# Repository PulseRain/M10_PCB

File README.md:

# M10_PCB
PCB Design File for PulseRain M10 board

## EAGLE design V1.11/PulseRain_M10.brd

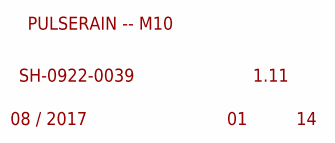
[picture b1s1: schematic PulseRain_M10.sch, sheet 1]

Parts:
GND: PULSERAIN_LOGO_BIGGER

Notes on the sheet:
1.11
SH-0922-0039
PULSERAIN -- M10
08 / 2017

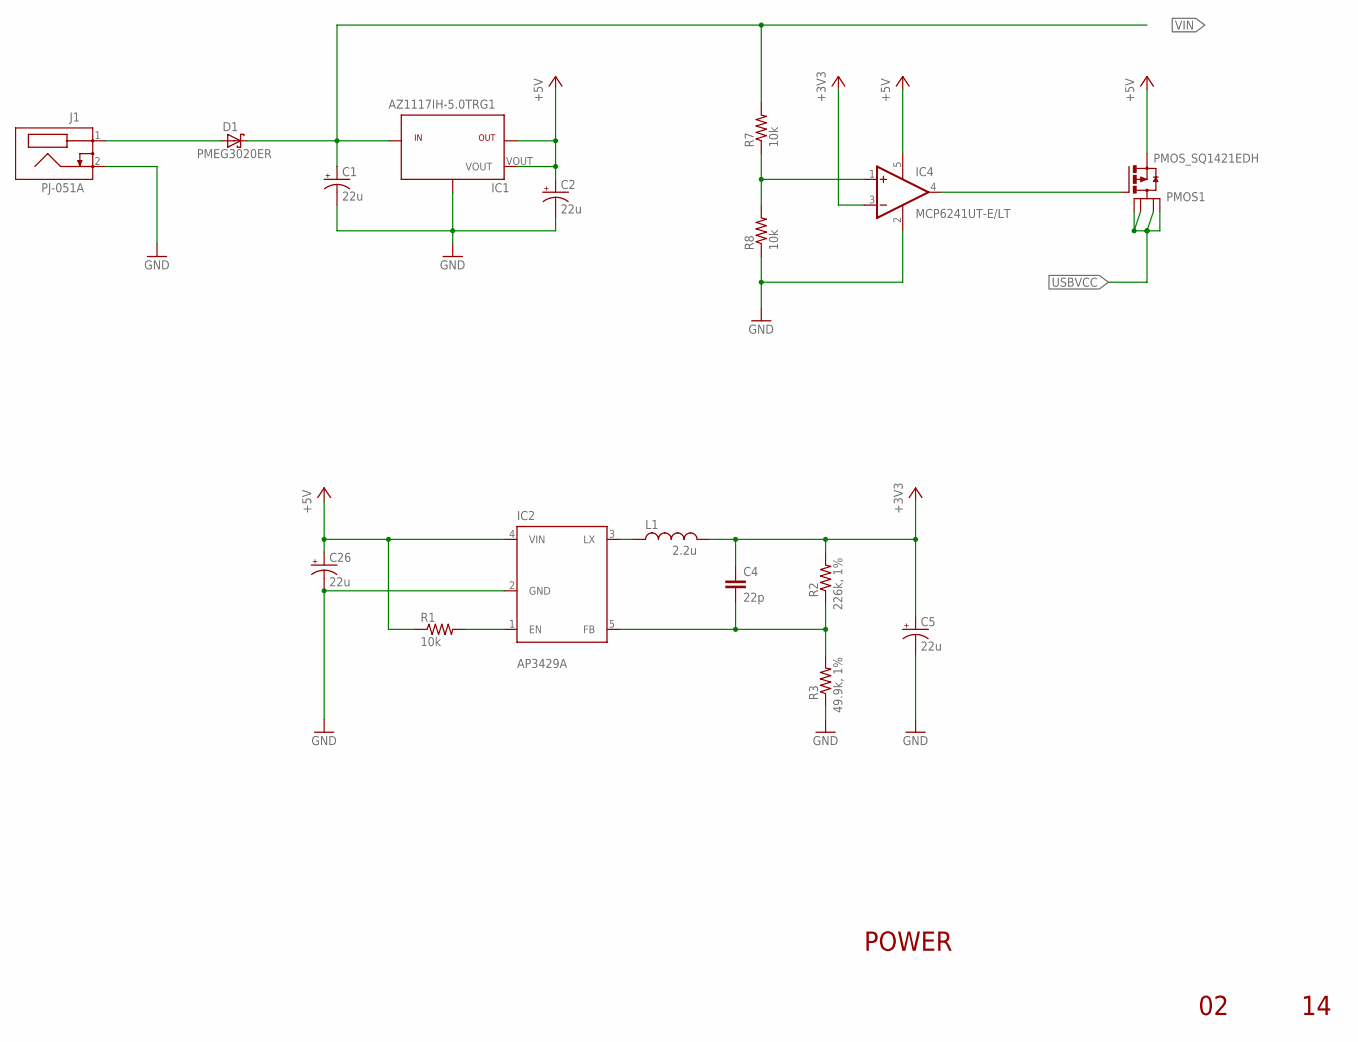
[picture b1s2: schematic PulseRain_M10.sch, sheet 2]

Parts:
C1, C2, C5, C26: 22u; PANASONIC_B
C4: 22p; 0603-CAP
D1: PMEG3020ER; SOD123W
IC1: AZ1117IH-5.0TRG1; SOT223
IC2: AP3429A; TSOT25
IC4: MCP6241UT-E/LT; SC-70-5
J1: PJ-051A
L1: 2.2u; DFE252012C
PMOS1: PMOS_SQ1421EDH; SC70-6L
R1, R7, R8: 10k; VISHAY-R-0603
R2: 226k, 1%; VISHAY-R-0603
R3: 49.9k, 1%; VISHAY-R-0603

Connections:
+3V3: C4.1, C5.+, IC4.3 (-IN), L1.2, R2.P$2 (2); also elsewhere on the board
+5V: C2.+, C26.+, IC1.2, IC1.VOUT, IC2.4 (VIN), IC4.5 (V+), PMOS1.4 (S), R1.P$1 (1); also elsewhere on the board
GND: C1.-, C2.-, C5.-, C26.-, IC1.1, IC2.2 (GND), IC4.2 (V-), J1.2, R3.P$1 (1), R8.P$1 (1); also elsewhere on the board
unnamed: D1.2, J1.1
unnamed: IC4.1 (+IN), R7.P$1 (1), R8.P$2 (2)
unnamed: IC2.3 (LX), L1.1
unnamed: IC2.1 (EN), R1.P$2 (2)
unnamed: C4.2, IC2.5 (FB), R2.P$1 (1), R3.P$2 (2)
unnamed: IC4.4 (OUT), PMOS1.3 (G)
USBVCC: PMOS1.1 (D1), PMOS1.2 (D2), PMOS1.5 (D3), PMOS1.6 (D4); also elsewhere on the board
VIN: C1.+, D1.1, IC1.3, R7.P$2 (2); also elsewhere on the board

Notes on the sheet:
POWER

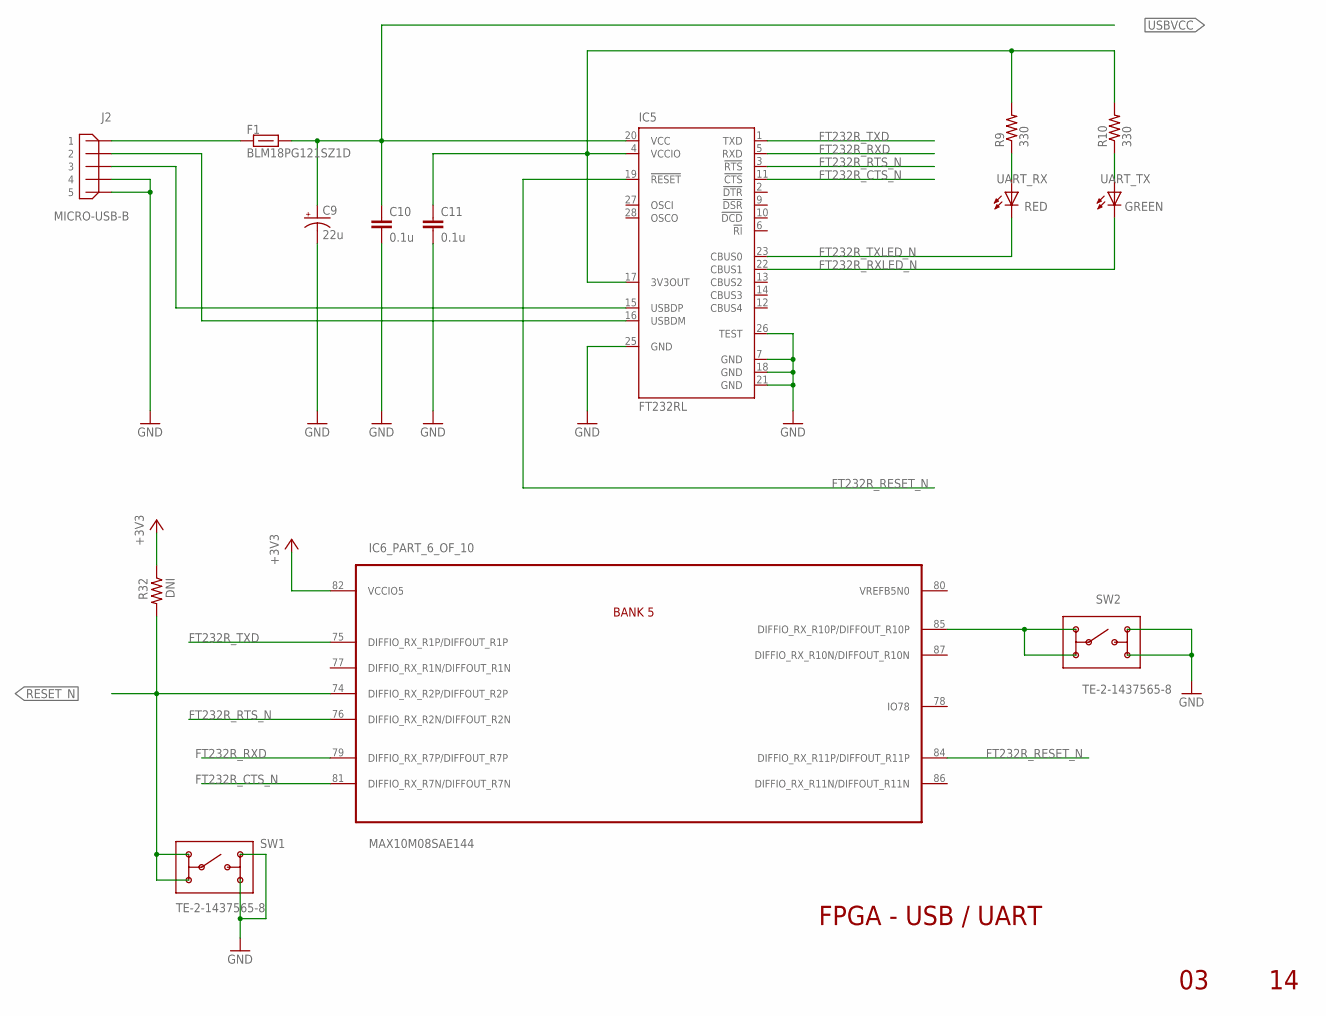
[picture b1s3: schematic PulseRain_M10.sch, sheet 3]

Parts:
C9: 22u; PANASONIC_B
C10, C11: 0.1u; 0603-CAP
F1: BLM18PG121SZ1D; 0603-BEAD
IC5: FT232RL; SSOP28
IC6: MAX10M08SAE144; EQFP144
J2: MICRO-USB-B; SD-47346-001
R9, R10: 330; VISHAY-R-0603
R32: DNI; VISHAY-R-0603
SW1, SW2: TE-2-1437565-8
UART_RX: RED; HARVATEK_0603
UART_TX: GREEN; HARVATEK_0603

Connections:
+3V3: IC6.82 (VCCIO5), R32.P$1 (1); also elsewhere on the board
FT232R_CTS_N: IC5.11 (!CTS), IC6.81 (DIFFIO_RX_R7N/DIFFOUT_R7N)
FT232R_RESET_N: IC5.19 (!RESET), IC6.84 (DIFFIO_RX_R11P/DIFFOUT_R11P)
FT232R_RTS_N: IC5.3 (!RTS), IC6.76 (DIFFIO_RX_R2N/DIFFOUT_R2N)
FT232R_RXD: IC5.5 (RXD), IC6.79 (DIFFIO_RX_R7P/DIFFOUT_R7P)
FT232R_RXLED_N: IC5.22 (CBUS1), UART_TX.C
FT232R_TXD: IC5.1 (TXD), IC6.75 (DIFFIO_RX_R1P/DIFFOUT_R1P)
FT232R_TXLED_N: IC5.23 (CBUS0), UART_RX.C
GND: C9.-, C10.2, C11.2, IC5.7 (GND), IC5.18 (GND), IC5.21 (GND), IC5.25 (GND), IC5.26 (TEST), J2.4, J2.5, SW1.3, SW1.4, SW2.3, SW2.4; also elsewhere on the board
unnamed: F1.1, J2.1
unnamed: IC6.85 (DIFFIO_RX_R10P/DIFFOUT_R10P), SW2.1, SW2.2
unnamed: C11.1, IC5.4 (VCCIO), IC5.17 (3V3OUT), R9.P$2 (2), R10.P$2 (2)
unnamed: R9.P$1 (1), UART_RX.A
unnamed: R10.P$1 (1), UART_TX.A
RESET_N: IC6.74 (DIFFIO_RX_R2P/DIFFOUT_R2P), R32.P$2 (2), SW1.1, SW1.2; also elsewhere on the board
USBVCC: C9.+, C10.1, F1.2, IC5.20 (VCC); also elsewhere on the board
USB_DATA_N: IC5.16 (USBDM), J2.2
USB_DATA_P: IC5.15 (USBDP), J2.3

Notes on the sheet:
FPGA - USB / UART

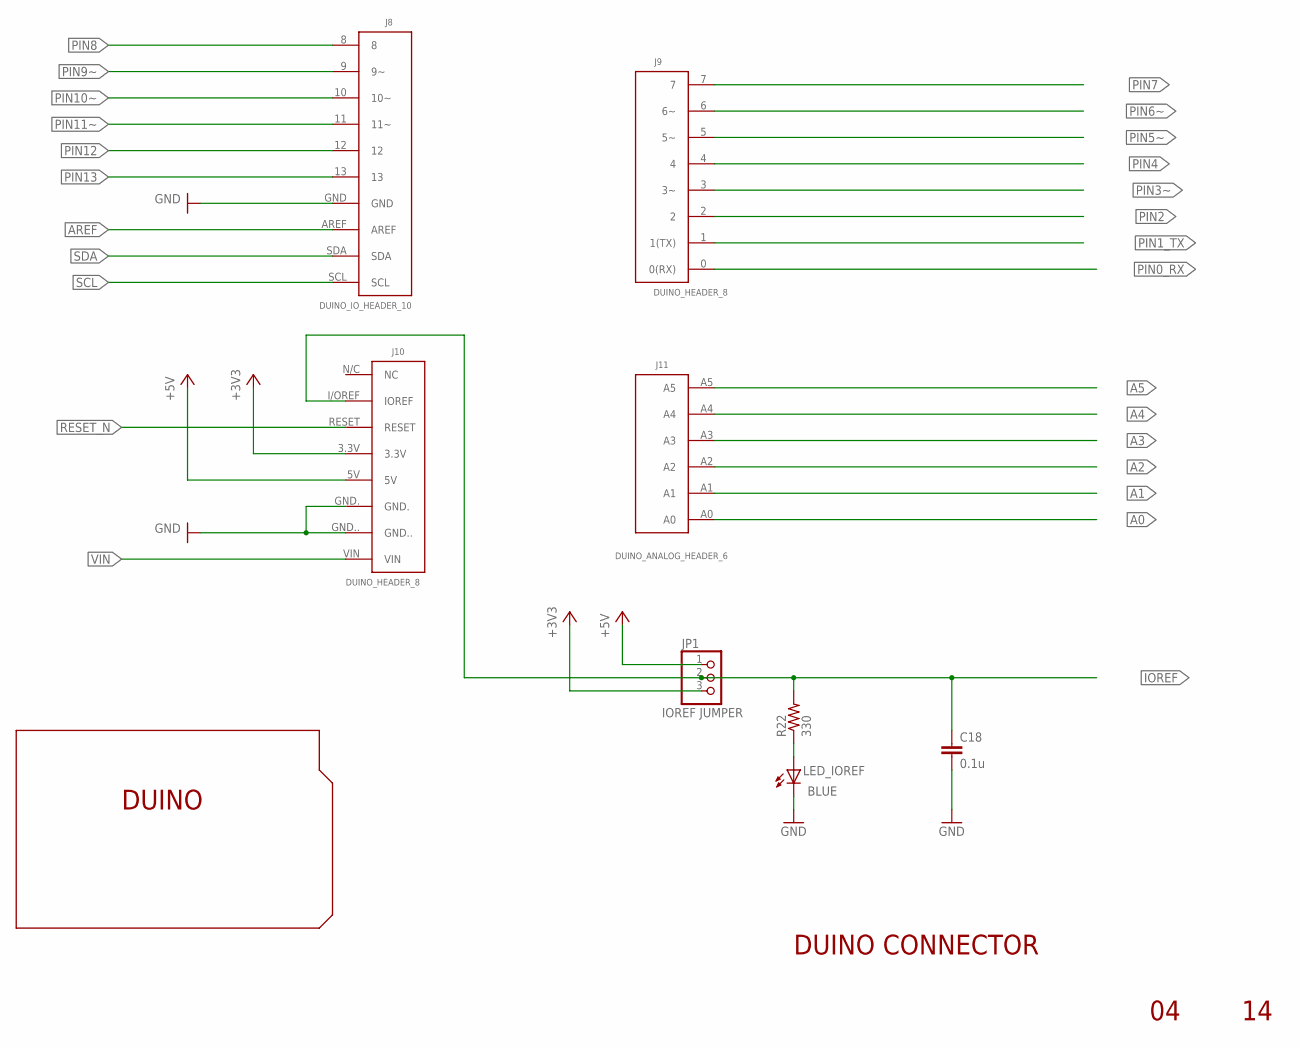
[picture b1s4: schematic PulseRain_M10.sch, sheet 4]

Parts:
C18: 0.1u; 0603-CAP
J8: DUINO_IO_HEADER_10
J9: DUINO_HEADER_8; DUINO_IO_HEADER_8
J10: DUINO_HEADER_8; DUINO_PWR_HEADER_8
J11: DUINO_ANALOG_HEADER_6
JP1: IOREF JUMPER; 1X03
LED_IOREF: BLUE; HARVATEK_0603
R22: 330; VISHAY-R-0603
U$8: DUINO

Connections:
+3V3: J10.3.3V, JP1.3; also elsewhere on the board
+5V: J10.5V, JP1.1; also elsewhere on the board
A0: J11.A0; also elsewhere on the board
A1: J11.A1; also elsewhere on the board
A2: J11.A2; also elsewhere on the board
A3: J11.A3; also elsewhere on the board
A4: J11.A4; also elsewhere on the board
A5: J11.A5; also elsewhere on the board
AREF: J8.AREF; also elsewhere on the board
GND: C18.2, J8.GND, J10.GND., J10.GND.., LED_IOREF.C; also elsewhere on the board
IOREF: C18.1, J10.I/OREF (IOREF), JP1.2, R22.P$2 (2); also elsewhere on the board
unnamed: LED_IOREF.A, R22.P$1 (1)
PIN0_RX: J9.0 (0(RX)); also elsewhere on the board
PIN1_TX: J9.1 (1(TX)); also elsewhere on the board
PIN2: J9.2; also elsewhere on the board
PIN3~: J9.3 (3~); also elsewhere on the board
PIN4: J9.4; also elsewhere on the board
PIN5~: J9.5 (5~); also elsewhere on the board
PIN6~: J9.6 (6~); also elsewhere on the board
PIN7: J9.7; also elsewhere on the board
PIN8: J8.8; also elsewhere on the board
PIN9~: J8.9 (9~); also elsewhere on the board
PIN10~: J8.10 (10~); also elsewhere on the board
PIN11~: J8.11 (11~); also elsewhere on the board
PIN12: J8.12; also elsewhere on the board
PIN13: J8.13; also elsewhere on the board
RESET_N: J10.RESET; also elsewhere on the board
SCL: J8.SCL; also elsewhere on the board
SDA: J8.SDA; also elsewhere on the board
VIN: J10.VIN; also elsewhere on the board

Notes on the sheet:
DUINO CONNECTOR

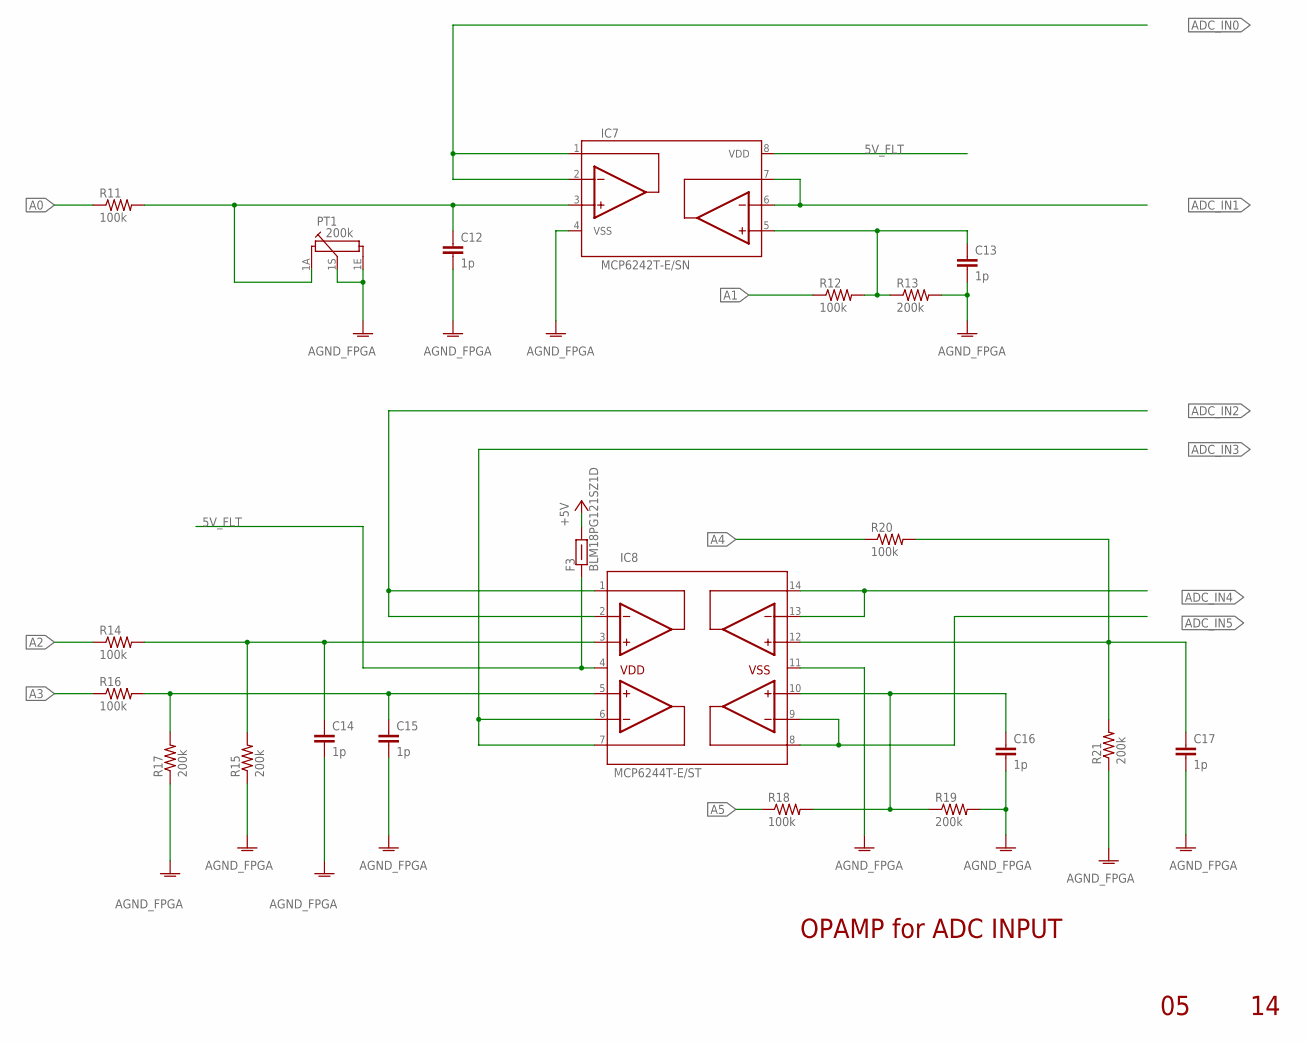
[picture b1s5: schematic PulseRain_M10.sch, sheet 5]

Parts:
C12, C13, C14, C15, C16, C17: 1p; 0603-CAP
F3: BLM18PG121SZ1D; 0603-BEAD
IC7: MCP6242T-E/SN; SOIC-SN-8
IC8: MCP6244T-E/ST; TSSOP-ST-14
PT1: 200k; PT10LV10
R11, R12, R14, R16, R18, R20: 100k; VISHAY-R-0603
R13, R15, R17, R19, R21: 200k; VISHAY-R-0603

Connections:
5V_FLT: F3.1, IC7.8 (VDD), IC8.4
+5V: F3.2; also elsewhere on the board
A0: R11.P$1 (1); also elsewhere on the board
A1: R12.P$1 (1); also elsewhere on the board
A2: R14.P$1 (1); also elsewhere on the board
A3: R16.P$1 (1); also elsewhere on the board
A4: R20.P$1 (1); also elsewhere on the board
A5: R18.P$1 (1); also elsewhere on the board
ADC_IN0: IC7.1, IC7.2; also elsewhere on the board
ADC_IN1: IC7.6, IC7.7; also elsewhere on the board
ADC_IN2: IC8.1, IC8.2; also elsewhere on the board
ADC_IN3: IC8.6, IC8.7; also elsewhere on the board
ADC_IN4: IC8.13, IC8.14; also elsewhere on the board
ADC_IN5: IC8.8, IC8.9; also elsewhere on the board
AGND_FPGA: C12.2, C13.2, C14.2, C15.2, C16.2, C17.2, IC7.4 (VSS), IC8.11, PT1.1E, PT1.1S, R13.P$2 (2), R15.P$1 (1), R17.P$1 (1), R19.P$2 (2), R21.P$1 (1); also elsewhere on the board
unnamed: C13.1, IC7.5, R12.P$2 (2), R13.P$1 (1)
unnamed: C16.1, IC8.10, R18.P$2 (2), R19.P$1 (1)
unnamed: C14.1, IC8.3, R14.P$2 (2), R15.P$2 (2)
unnamed: C15.1, IC8.5, R16.P$2 (2), R17.P$2 (2)
unnamed: C12.1, IC7.3, PT1.1A, R11.P$2 (2)
unnamed: C17.1, IC8.12, R20.P$2 (2), R21.P$2 (2)

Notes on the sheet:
OPAMP for ADC INPUT

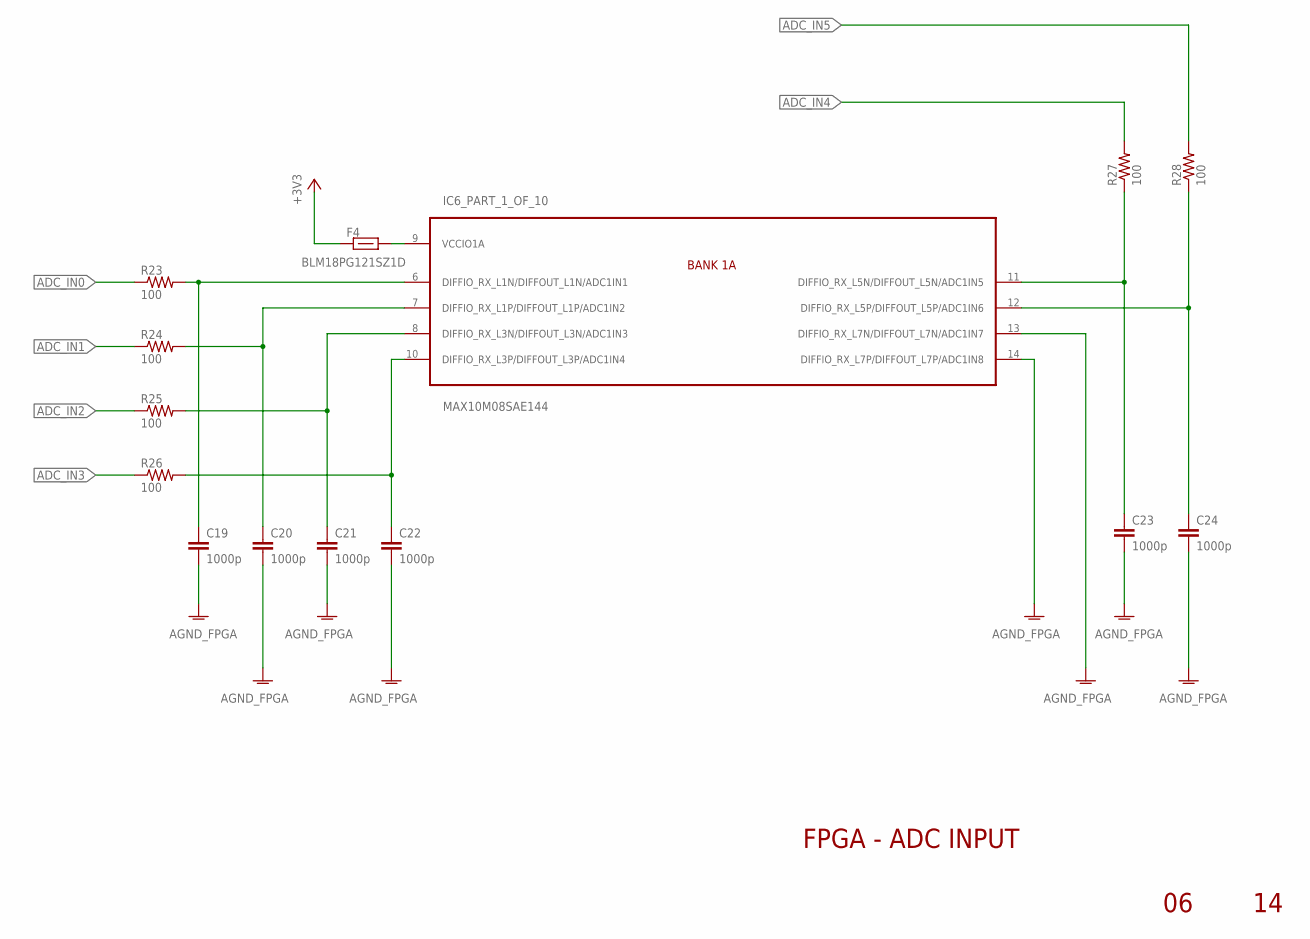
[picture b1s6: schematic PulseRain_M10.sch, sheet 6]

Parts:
C19, C20, C21, C22, C23, C24: 1000p; VISHAY-R-0603
F4: BLM18PG121SZ1D; 0603-BEAD
IC6: MAX10M08SAE144; EQFP144
R23, R24, R25, R26, R27, R28: 100; VISHAY-R-0603

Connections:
+3V3: F4.1; also elsewhere on the board
ADC_IN0: R23.P$1 (1); also elsewhere on the board
ADC_IN1: R24.P$1 (1); also elsewhere on the board
ADC_IN2: R25.P$1 (1); also elsewhere on the board
ADC_IN3: R26.P$1 (1); also elsewhere on the board
ADC_IN4: R27.P$2 (2); also elsewhere on the board
ADC_IN5: R28.P$2 (2); also elsewhere on the board
AGND_FPGA: C19.P$2 (2), C20.P$2 (2), C21.P$2 (2), C22.P$2 (2), C23.P$2 (2), C24.P$2 (2), IC6.13 (DIFFIO_RX_L7N/DIFFOUT_L7N/ADC1IN7), IC6.14 (DIFFIO_RX_L7P/DIFFOUT_L7P/ADC1IN8); also elsewhere on the board
unnamed: C23.P$1 (1), IC6.11 (DIFFIO_RX_L5N/DIFFOUT_L5N/ADC1IN5), R27.P$1 (1)
unnamed: C19.P$1 (1), IC6.6 (DIFFIO_RX_L1N/DIFFOUT_L1N/ADC1IN1), R23.P$2 (2)
unnamed: C20.P$1 (1), IC6.7 (DIFFIO_RX_L1P/DIFFOUT_L1P/ADC1IN2), R24.P$2 (2)
unnamed: C21.P$1 (1), IC6.8 (DIFFIO_RX_L3N/DIFFOUT_L3N/ADC1IN3), R25.P$2 (2)
unnamed: C22.P$1 (1), IC6.10 (DIFFIO_RX_L3P/DIFFOUT_L3P/ADC1IN4), R26.P$2 (2)
unnamed: C24.P$1 (1), IC6.12 (DIFFIO_RX_L5P/DIFFOUT_L5P/ADC1IN6), R28.P$1 (1)
unnamed: F4.2, IC6.9 (VCCIO1A)

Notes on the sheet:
FPGA - ADC INPUT

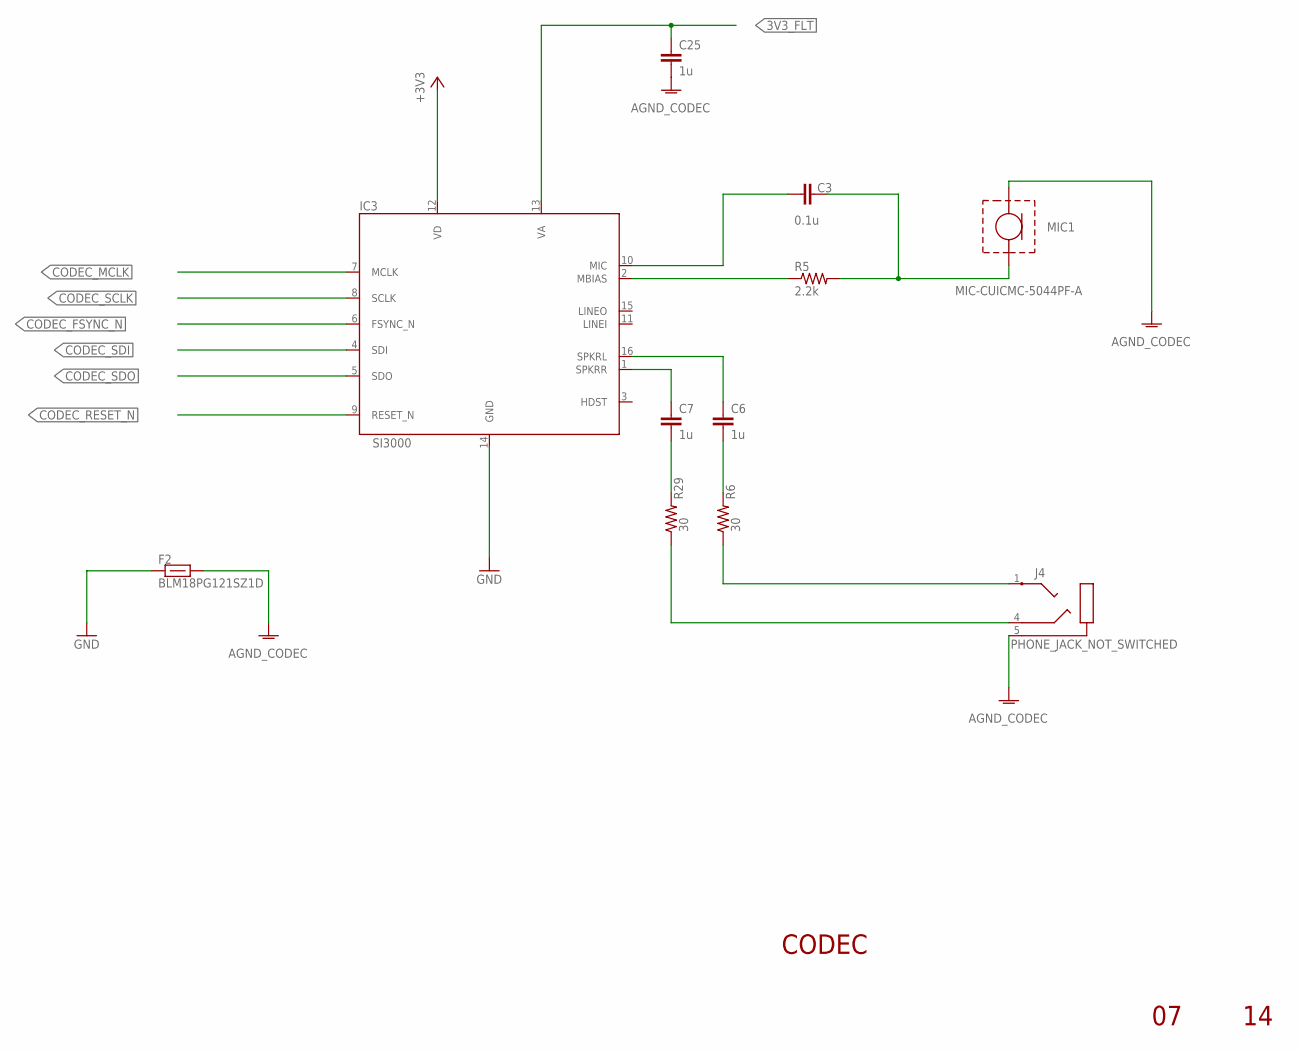
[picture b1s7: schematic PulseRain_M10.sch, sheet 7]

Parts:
C3: 0.1u; 0603-CAP
C6, C7, C25: 1u; VISHAY-R-0603
F2: BLM18PG121SZ1D; 0603-BEAD
IC3: SI3000; SOIC-16
J4: PHONE_JACK_NOT_SWITCHED
MIC1: MIC-CUICMC-5044PF-A; CMC-5044PF-A
R5: 2.2k; VISHAY-R-0603
R6, R29: 30; VISHAY-R-0603

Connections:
3V3_FLT: C25.P$1 (1), IC3.13 (VA); also elsewhere on the board
+3V3: IC3.12 (VD); also elsewhere on the board
AGND_CODEC: C25.P$2 (2), F2.2, J4.5, MIC1.1 (2)
CODEC_FSYNC_N: IC3.6 (FSYNC_N); also elsewhere on the board
CODEC_MCLK: IC3.7 (MCLK); also elsewhere on the board
CODEC_RESET_N: IC3.9 (RESET_N); also elsewhere on the board
CODEC_SCLK: IC3.8 (SCLK); also elsewhere on the board
CODEC_SDI: IC3.4 (SDI); also elsewhere on the board
CODEC_SDO: IC3.5 (SDO); also elsewhere on the board
GND: F2.1, IC3.14 (GND); also elsewhere on the board
unnamed: C3.1, IC3.10 (MIC)
unnamed: C6.P$1 (1), IC3.16 (SPKRL)
unnamed: C3.2, MIC1.2 (1), R5.P$2 (2)
unnamed: IC3.2 (MBIAS), R5.P$1 (1)
unnamed: C7.P$1 (1), IC3.1 (SPKRR)
unnamed: C7.P$2 (2), R29.P$2 (2)
unnamed: C6.P$2 (2), R6.P$2 (2)
unnamed: J4.1, R6.P$1 (1)
unnamed: J4.4, R29.P$1 (1)

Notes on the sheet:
CODEC

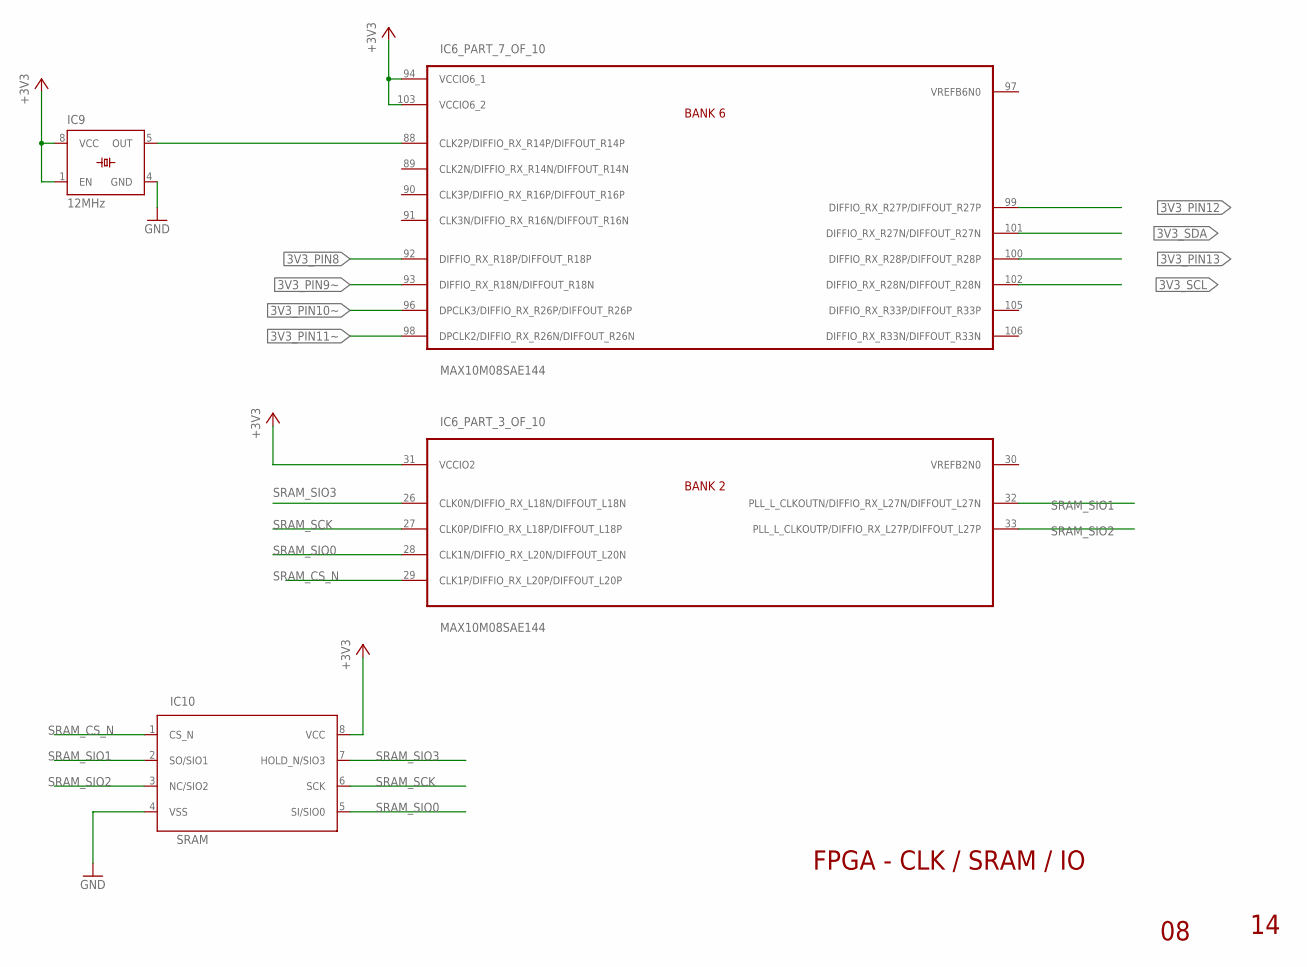
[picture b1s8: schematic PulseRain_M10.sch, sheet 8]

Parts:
IC6: MAX10M08SAE144; EQFP144
IC9: 12MHz; ACHL-DIP
IC10: SRAM; TSSOP-ST-8

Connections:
3V3_PIN8: IC6.92 (DIFFIO_RX_R18P/DIFFOUT_R18P); also elsewhere on the board
3V3_PIN9~: IC6.93 (DIFFIO_RX_R18N/DIFFOUT_R18N); also elsewhere on the board
3V3_PIN10~: IC6.96 (DPCLK3/DIFFIO_RX_R26P/DIFFOUT_R26P); also elsewhere on the board
3V3_PIN11~: IC6.98 (DPCLK2/DIFFIO_RX_R26N/DIFFOUT_R26N); also elsewhere on the board
3V3_PIN12: IC6.99 (DIFFIO_RX_R27P/DIFFOUT_R27P); also elsewhere on the board
3V3_PIN13: IC6.100 (DIFFIO_RX_R28P/DIFFOUT_R28P); also elsewhere on the board
3V3_SCL: IC6.102 (DIFFIO_RX_R28N/DIFFOUT_R28N); also elsewhere on the board
3V3_SDA: IC6.101 (DIFFIO_RX_R27N/DIFFOUT_R27N); also elsewhere on the board
+3V3: IC6.31 (VCCIO2), IC6.94 (VCCIO6_1), IC6.103 (VCCIO6_2), IC9.1 (EN), IC9.8 (VCC), IC10.8 (VCC); also elsewhere on the board
GND: IC9.4 (GND), IC10.4 (VSS); also elsewhere on the board
unnamed: IC6.88 (CLK2P/DIFFIO_RX_R14P/DIFFOUT_R14P), IC9.5 (OUT)
SRAM_CS_N: IC6.29 (CLK1P/DIFFIO_RX_L20P/DIFFOUT_L20P), IC10.1 (CS_N)
SRAM_SCK: IC6.27 (CLK0P/DIFFIO_RX_L18P/DIFFOUT_L18P), IC10.6 (SCK)
SRAM_SIO0: IC6.28 (CLK1N/DIFFIO_RX_L20N/DIFFOUT_L20N), IC10.5 (SI/SIO0)
SRAM_SIO1: IC6.32 (PLL_L_CLKOUTN/DIFFIO_RX_L27N/DIFFOUT_L2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), IC10.2 (SO/SIO1)
SRAM_SIO2: IC6.33 (PLL_L_CLKOUTP/DIFFIO_RX_L27P/DIFFOUT_L2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), IC10.3 (NC/SIO2)
SRAM_SIO3: IC6.26 (CLK0N/DIFFIO_RX_L18N/DIFFOUT_L18N), IC10.7 (HOLD_N/SIO3)

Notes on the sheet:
FPGA - CLK / SRAM / IO

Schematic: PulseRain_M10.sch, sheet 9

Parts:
IC6: MAX10M08SAE144; EQFP144

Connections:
3V3_PIN0_RX: IC6.50 (DIFFIO_TX_RX_B9N/DIFFOUT_B9N); also elsewhere on the board
3V3_PIN1_TX: IC6.52 (DIFFIO_TX_RX_B9P/DIFFOUT_B9P); also elsewhere on the board
3V3_PIN2: IC6.54 (IO54); also elsewhere on the board
3V3_PIN3~: IC6.55 (DIFFIO_TX_RX_B12N/DIFFOUT_B12N); also elsewhere on the board
3V3_PIN4: IC6.56 (DIFFIO_TX_RX_B12P/DIFFOUT_B12P); also elsewhere on the board
3V3_PIN5~: IC6.57 (DIFFIO_TX_RX_B14N/DIFFOUT_B14N); also elsewhere on the board
3V3_PIN6~: IC6.58 (DIFFIO_TX_RX_B14P/DIFFOUT_B14P); also elsewhere on the board
3V3_PIN7: IC6.59 (DIFFIO_TX_RX_B16N/DIFFOUT_B16N); also elsewhere on the board
+3V3: IC6.40 (VCCIO3_1), IC6.49 (VCCIO3_2); also elsewhere on the board
CODEC_FSYNC_N: IC6.43 (DIFFIO_TX_RX_B3P/DIFFOUT_B3P); also elsewhere on the board
CODEC_MCLK: IC6.41 (DIFFIO_TX_RX_B3N/DIFFOUT_B3N); also elsewhere on the board
CODEC_RESET_N: IC6.39 (DIFFIO_TX_RX_B1P/DIFFOUT_B1P); also elsewhere on the board
CODEC_SCLK: IC6.38 (DIFFIO_TX_RX_B1N/DIFFOUT_B1N); also elsewhere on the board
CODEC_SDI: IC6.45 (DIFFIO_TX_RX_B5P/DIFFOUT_B5P); also elsewhere on the board
CODEC_SDO: IC6.44 (DIFFIO_TX_RX_B5N/DIFFOUT_B5N); also elsewhere on the board
JTAG_PIN6: IC6.46 (DIFFIO_TX_RX_B7N/DIFFOUT_B7N); also elsewhere on the board
JTAG_PIN7: IC6.60 (DIFFIO_TX_RX_B16P/DIFFOUT_B16P); also elsewhere on the board
JTAG_PIN8: IC6.47 (DIFFIO_TX_RX_B7P/DIFFOUT_B7P); also elsewhere on the board

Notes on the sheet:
FPGA - PUSH BUTTON / IO

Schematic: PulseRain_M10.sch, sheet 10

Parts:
IC6: MAX10M08SAE144; EQFP144
J7: ALTERA_JTAG; 2X05
JP2: DNI; 1X02
R33, R34, R35: 10k; VISHAY-R-0603
R39: 1k; VISHAY-R-0603

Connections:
+3V3: IC6.23 (VCCIO1B), J7.4, R33.P$1 (1), R34.P$2 (2), R35.P$2 (2); also elsewhere on the board
GND: J7.2, J7.10, JP2.2, R39.P$1 (1); also elsewhere on the board
JTAGEN: IC6.15 (JTAGEN), JP2.1, R33.P$2 (2)
JTAG_PIN6: J7.6; also elsewhere on the board
JTAG_PIN7: J7.7; also elsewhere on the board
JTAG_PIN8: J7.8; also elsewhere on the board
TCK: IC6.18 (TCK/DIFFIO_RX_L11P/DIFFOUT_L11P), J7.1, R39.P$2 (2)
TDI: IC6.19 (TDI/DIFFIO_RX_L12N/DIFFOUT_L12N), J7.9, R34.P$1 (1)
TDO: IC6.20 (TDO/DIFFIO_RX_L12P/DIFFOUT_L12P), J7.3
TMS: IC6.16 (TMS/DIFFIO_RX_L11N/DIFFOUT_L11N), J7.5, R35.P$1 (1)

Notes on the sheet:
FPGA - JTAG

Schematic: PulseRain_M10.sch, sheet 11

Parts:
IC6: MAX10M08SAE144; EQFP144
IC11: 0472192001; MOLEX-0472192001

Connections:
+3V3: IC6.67 (VCCIO4), IC6.117 (VCCIO7), IC11.4 (VDD); also elsewhere on the board
GND: IC11.6 (VSS); also elsewhere on the board
MICRO_SD_CD_DAT3: IC6.69 (DIFFIO_TX_RX_B27N/DIFFOUT_B27N), IC11.2 (CD/DAT3)
MICRO_SD_CLK: IC6.65 (DIFFIO_TX_RX_B23P/DIFFOUT_B23P), IC11.5 (CLK)
MICRO_SD_CMD: IC6.66 (IO66), IC11.3 (CMD)
MICRO_SD_DAT0: IC6.64 (DIFFIO_TX_RX_B23N/DIFFOUT_B23N), IC11.7 (DAT0)
MICRO_SD_DAT1: IC6.62 (IO62), IC11.8 (DAT1)
MICRO_SD_DAT2: IC6.70 (DIFFIO_TX_RX_B27P/DIFFOUT_B27P), IC11.1 (DAT2)

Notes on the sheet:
FPGA - MICRO SD

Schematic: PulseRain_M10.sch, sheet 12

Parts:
IC6: MAX10M08SAE144; EQFP144
JP6: BOOT IMAGE SELECT; 1X02
LED1: GREEN; HARVATEK_0603
LED2: RED; HARVATEK_0603
LED3: BLUE; HARVATEK_0603
R36, R37, R38, R40, R41: 10k; VISHAY-R-0603
R42, R43, R47: 330; VISHAY-R-0603

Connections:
+3V3: IC6.128 (VCCIO8_1), IC6.139 (VCCIO8_2), R36.P$1 (1), R37.P$2 (2), R38.P$2 (2), R40.P$1 (1), R41.P$1 (1), R42.P$2 (2), R43.P$2 (2), R47.P$2 (2); also elsewhere on the board
GND: JP6.2; also elsewhere on the board
unnamed: IC6.132 (DIFFIO_RX_T22P/DIFFOUT_T22P), LED3.C
unnamed: IC6.129 (NCONFIG), R36.P$2 (2)
unnamed: IC6.136 (NSTATUS/DIFFIO_RX_T24P/DIFFOUT_T24P), R37.P$1 (1)
unnamed: IC6.138 (CONF_DONE/DIFFIO_RX_T24N/DIFFOUT_T24N), R38.P$1 (1)
unnamed: IC6.126 (CONFIG_SEL), JP6.1, R40.P$2 (2)
unnamed: IC6.121 (DEV_CLRN/DIFFIO_RX_T16N/DIFFOUT_T16N), R41.P$2 (2)
unnamed: IC6.130 (DIFFIO_RX_T20P/DIFFOUT_T20P), LED1.C
unnamed: IC6.131 (DIFFIO_RX_T20N/DIFFOUT_T20N), LED2.C
unnamed: LED1.A, R42.P$1 (1)
unnamed: LED2.A, R43.P$1 (1)
unnamed: LED3.A, R47.P$1 (1)

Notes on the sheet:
FPGA - LED

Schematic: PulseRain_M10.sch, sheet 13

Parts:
F5, F6, F7, F8: BLM18PG121SZ1D; 0603-BEAD
IC6: MAX10M08SAE144; EQFP144

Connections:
3V3_FLT: F6.2, IC6.34 (VCCA2), IC6.35 (VCCA1), IC6.71 (VCCA5), IC6.107 (VCCA3); also elsewhere on the board
+3V3: F5.1, F6.1, IC6.1 (VCC_ONE10), IC6.36 (VCC_ONE5), IC6.37 (VCC_ONE4), IC6.51 (VCC_ONE3), IC6.72 (VCC_ONE1), IC6.73 (VCC_ONE2), IC6.108 (VCC_ONE9), IC6.109 (VCC_ONE8), IC6.115 (VCC_ONE7), IC6.144 (VCC_ONE6); also elsewhere on the board
AGND_FPGA: F7.1, F8.2, IC6.3 (ANAIN1); also elsewhere on the board
AREF: IC6.5 (ADC_REF); also elsewhere on the board
GND: F8.1, IC6.42 (GND6), IC6.53 (GND5), IC6.63 (GND4), IC6.68 (GND3), IC6.83 (GND13), IC6.95 (GND1), IC6.104 (GND12), IC6.116 (GND11), IC6.125 (GND10), IC6.133 (GND9), IC6.137 (GND8), IC6.142 (GND7); also elsewhere on the board
unnamed: F5.2, IC6.2 (VCCA6), IC6.143 (VCCA4)
unnamed: F7.2, IC6.4 (REFGND/GND2)

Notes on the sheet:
FPGA - Power / Ground

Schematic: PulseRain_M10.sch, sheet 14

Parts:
IC12, IC13: TXS0108EPWR; TSSOP8

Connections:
3V3_PIN0_RX: IC12.1; also elsewhere on the board
3V3_PIN1_TX: IC12.3; also elsewhere on the board
3V3_PIN2: IC12.4; also elsewhere on the board
3V3_PIN3~: IC12.5; also elsewhere on the board
3V3_PIN4: IC12.6; also elsewhere on the board
3V3_PIN5~: IC12.7; also elsewhere on the board
3V3_PIN6~: IC12.8; also elsewhere on the board
3V3_PIN7: IC12.9; also elsewhere on the board
3V3_PIN8: IC13.1; also elsewhere on the board
3V3_PIN9~: IC13.3; also elsewhere on the board
3V3_PIN10~: IC13.4; also elsewhere on the board
3V3_PIN11~: IC13.5; also elsewhere on the board
3V3_PIN12: IC13.6; also elsewhere on the board
3V3_PIN13: IC13.7; also elsewhere on the board
3V3_SCL: IC13.9; also elsewhere on the board
3V3_SDA: IC13.8; also elsewhere on the board
+3V3: IC12.2, IC12.10, IC13.2, IC13.10; also elsewhere on the board
GND: IC12.11, IC13.11; also elsewhere on the board
IOREF: IC12.19, IC13.19; also elsewhere on the board
PIN0_RX: IC12.20; also elsewhere on the board
PIN1_TX: IC12.18; also elsewhere on the board
PIN2: IC12.17; also elsewhere on the board
PIN3~: IC12.16; also elsewhere on the board
PIN4: IC12.15; also elsewhere on the board
PIN5~: IC12.14; also elsewhere on the board
PIN6~: IC12.13; also elsewhere on the board
PIN7: IC12.12; also elsewhere on the board
PIN8: IC13.20; also elsewhere on the board
PIN9~: IC13.18; also elsewhere on the board
PIN10~: IC13.17; also elsewhere on the board
PIN11~: IC13.16; also elsewhere on the board
PIN12: IC13.15; also elsewhere on the board
PIN13: IC13.14; also elsewhere on the board
SCL: IC13.12; also elsewhere on the board
SDA: IC13.13; also elsewhere on the board

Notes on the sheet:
Voltage Level Translator

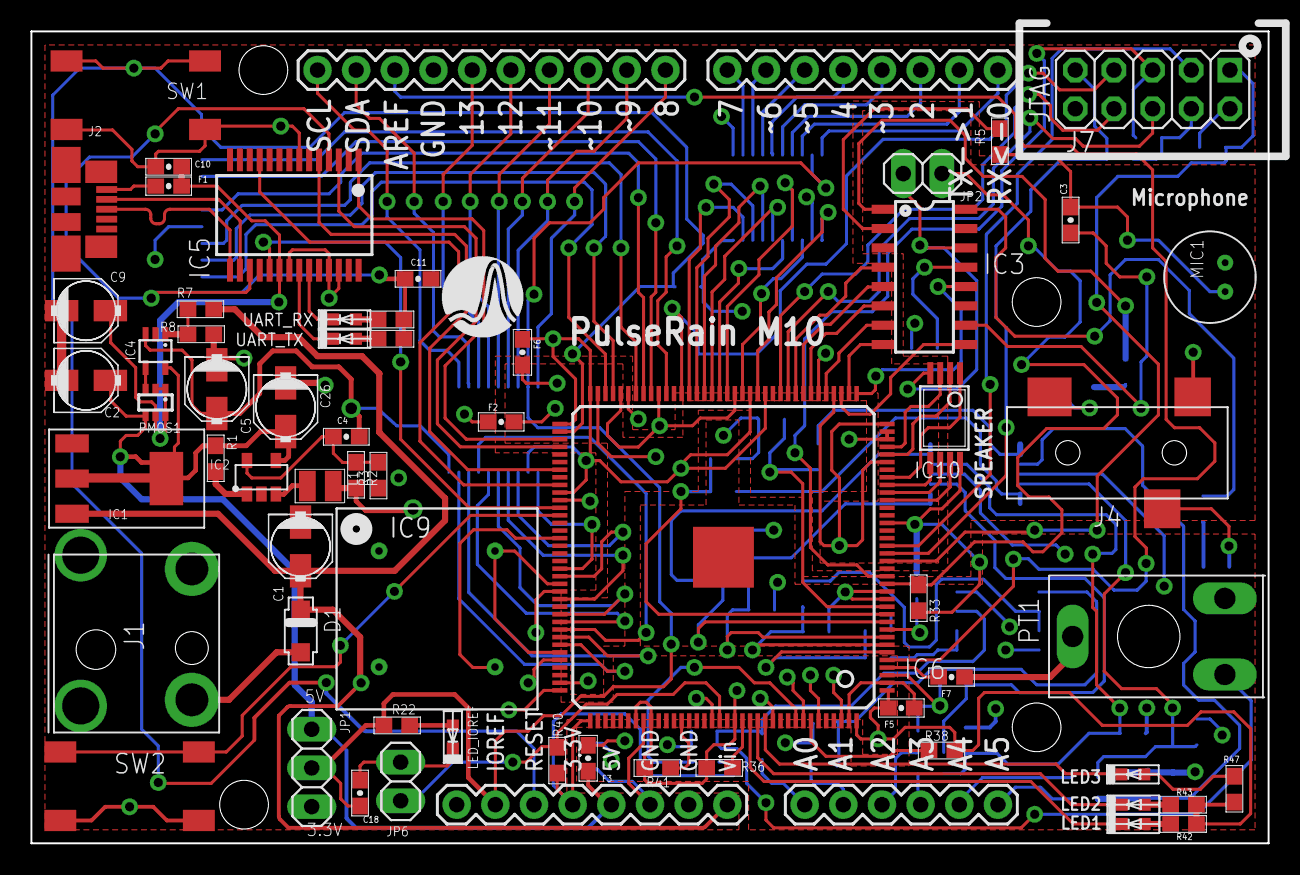
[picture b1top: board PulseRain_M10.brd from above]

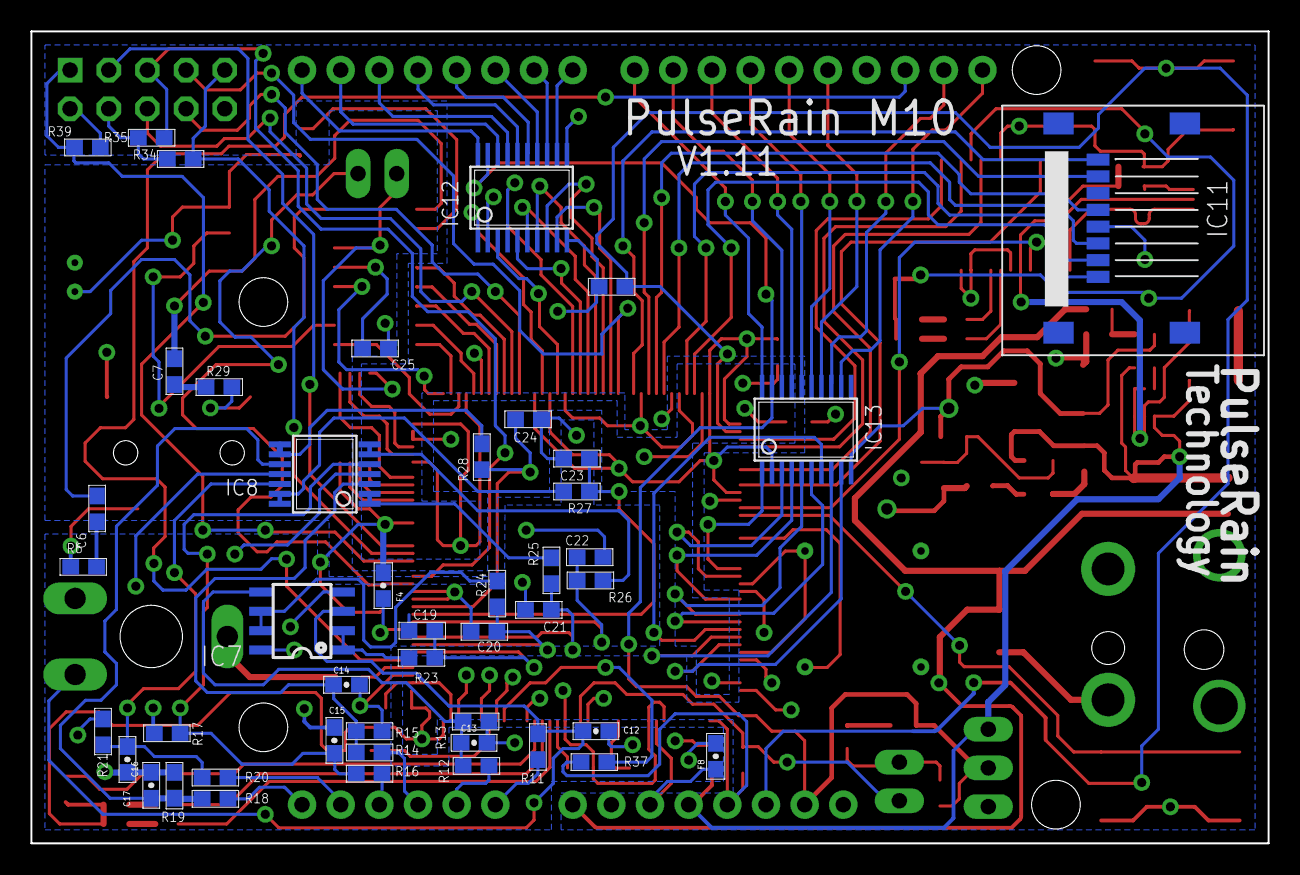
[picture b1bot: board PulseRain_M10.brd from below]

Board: 4 copper layers, 81.3 x 53.3 mm, 113 parts (46 on the bottom side), 139 nets.

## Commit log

2017-02-23 rename LICENSE to LICENSE.md
2017-02-23 add V0.9 (code name Mustang Duino)
2017-04-23 add V1.0, pilot run for production
2017-11-02 add V1.11 schematic and layout
2017-11-02 add hardware manual
2017-11-12 add M10_ATP.pdf
2017-11-20 add pdf schematic for V1.0
